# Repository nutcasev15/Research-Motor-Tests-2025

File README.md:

# Research Motor Tests 2025
FireSide PCB & Firmware and GroundSide Software

## Project Overview
This repository contains the support equipment and software developed for the 2025 research motor test campaign. The project includes both the **FireSide** embedded system with its PCB design (responsible for ignition, data sampling, and SD card logging) and the **GroundSide** software telemetry & command interface.

---

## Test Execution Hardware
The `pcb` directory contains the FireSide PCB schematics, design, and manufacturing Bill of Materials as a KiCAD 9.0 project. The FireSide system includes ignition control, data acquisition, and high speed logging built around a Nucleo32 STM32L412KB board. Key capabilities include:

- Upto 6 parallel >3 kHz channels logging using 12-bit ADC with a circular buffer
- Binary logging to SD card with onboard CSV conversion utility
- Reyax RYLR LoRa‑based command, debugging, and telemetry exchange
- MOSFET D4184 module‑based ignition control with safety interlocks
- Deterministic, debugger ready, and reliable state‑machine‑driven operation

This architecture aims to improve fault detection, reliability, and repeatability. The architecture is inspired by ECSS requirements on space operations software and commercial electronic components.

## Test Execution Software
The `src` directory contains the embedded & Python software developed for the test campaign.

### FireSide PCB Firmware (`src/FireSide/`)

| File | Description |
|------|-------------|
| **main.cpp** | Assembles the system state machine and runs the main execution loop. |
| **States.cpp** | Implements the BOOT, SAFE, ARM, LAUNCH, LOGGING, CONVERT & FAILURE states. Defines the state transition logic. |
| **DMADAQ.cpp** | Configures DMA‑based ADC sampling and SD card logging through the STM32 L4 HAL. |
| **Interfaces.hpp** | Defines shared HW interfaces for UART serials, IO pins and ADC hardware used across the FireSide firmware. Allows debugging through a USB Serial Monitor. |
| **ConvertLog.py** | Post‑processes FireSide binary log files into CSV format. Useful after testing to extract sensor data from large files if onboard conversion fails. |

### GroundSide (`src/GroundSide/`)

| File | Description |
|------|-------------|
| **GroundSide.py** | Sends commands and receives telemetry from the FireSide PCB via a Reyax RYLR LoRa chip through a USB-Serial module. Provides a traceable interface for executing a motor test. |

---

## References

1. [STM32 Nucleo‑32 Boards (MB1180) User Manual](
  https://www.st.com/resource/en/user_manual/um1956-stm32-nucleo32-boards-mb1180-stmicroelectronics.pdf
)
2. [STM32L4 HAL and Low‑Layer Drivers](
  https://www.st.com/resource/en/user_manual/um1884-description-of-stm32l4l4-hal-and-lowlayer-drivers-stmicroelectronics.pdf
)
3. [STM32L41x/42x/43x/44x/45x/46x Reference Manual](
  https://www.st.com/resource/en/reference_manual/rm0394-stm32l41xxx42xxx43xxx44xxx45xxx46xxx-advanced-armbased-32bit-mcus-stmicroelectronics.pdf
)
4. [Cortex‑M4 Programming Manual](
  https://www.st.com/resource/en/programming_manual/pm0214-stm32-cortexm4-mcus-and-mpus-programming-manual-stmicroelectronics.pdf
)
5. [STM32L412xx/422xB Device Errata](
  https://www.st.com/resource/en/errata_sheet/es0456-stm32l412xx422xb-device-errata-stmicroelectronics.pdf
)
6. [PlatformIO STM32 Platform Documentation](
  https://docs.platformio.org/en/latest/platforms/ststm32.html
)
7. [Reyax RYLR993 Transceiver Module](
  https://robu.in/product/reyax-rylr993_lite-868-915mhz-lorawan-transceiver-module-helium-compatible-lite-evaluation-boarddip-version/
)
8. [CP2102 USB to TTL Serial Converter Module](
  https://robu.in/product/cp-2102-6-pin/
)

---

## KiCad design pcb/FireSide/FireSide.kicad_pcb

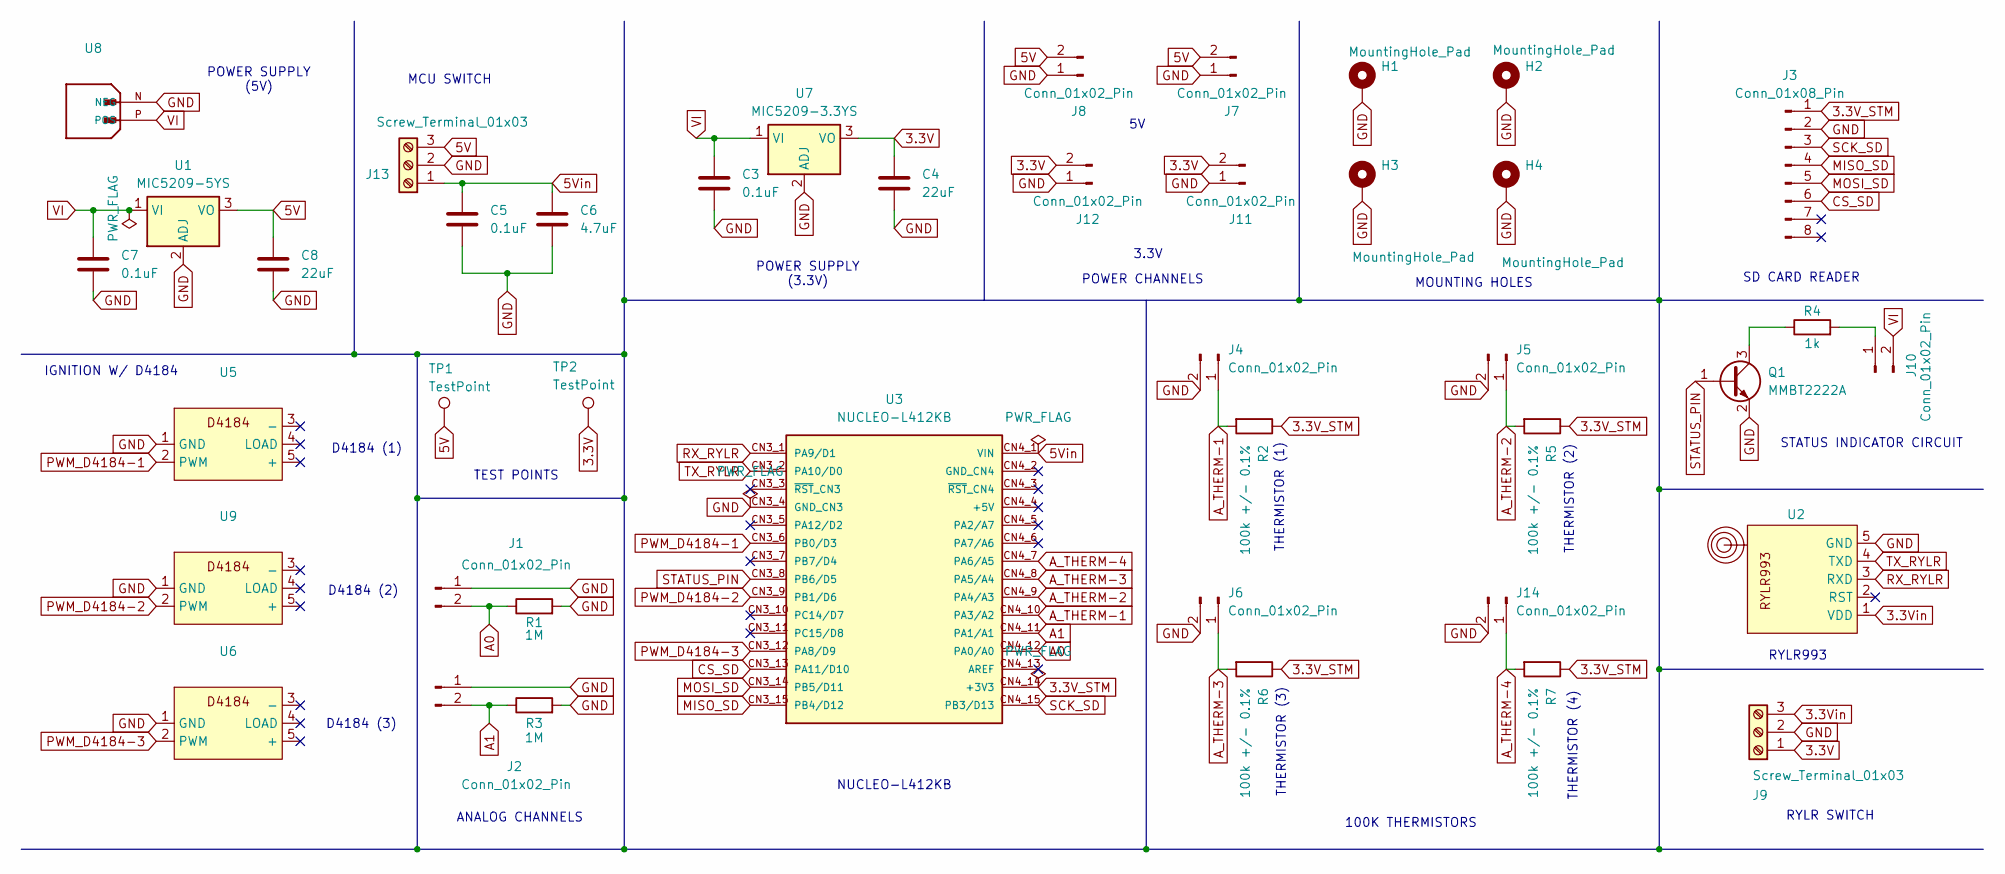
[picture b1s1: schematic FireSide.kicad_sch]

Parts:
C3, C5, C7: 0.1uF; C_0805_2012Metric
C4, C8: 22uF; C_0805_2012Metric
C6: 4.7uF; C_0805_2012Metric
H1, H2, H3, H4: MountingHole_Pad; MountingHole_4.3mm_M4_DIN965_Pad
J1, J2, J4, J5, J6, J7, J8, J10, J11, J12, J14: Conn_01x02_Pin; JST_XH_B2B-XH-A_1x02_P2.50mm_Vertical
J3: Conn_01x08_Pin; PinHeader_1x08_P2.54mm_Vertical
J9, J13: Screw_Terminal_01x03; TerminalBlock_MaiXu_MX126-5.0-03P_1x03_P5.00mm
Q1: MMBT2222A; SOT-23
R1, R3: 1M; R_Axial_DIN0204_L3.6mm_D1.6mm_P5.08mm_Horizontal
R2, R5, R6, R7: 100k +/- 0.1%; R_0805_2012Metric
R4: 1k; R_0805_2012Metric
TP1, TP2: TestPoint; TestPoint_Loop_D2.60mm_Drill1.6mm_Beaded
U1: MIC5209-5YS; SOT-223-3_TabPin2
U2: RYLR993
U3: NUCLEO-L412KB; PARTREV 8
U5, U6, U9: D4184
U7: MIC5209-3.3YS; SOT-223-3_TabPin2
U8: XT60-M

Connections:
3.3V: C4.1, J9.1, J11.2, J12.2, TP2.1, U7.3 (VO)
3.3V_STM: J3.1, R2.1, R5.1, R6.1, R7.1, U3.CN4_14 (+3V3)
3.3Vin: J9.3, U2.1 (VDD)
5V: C8.1, J7.2, J8.2, J13.3, TP1.1, U1.3 (VO)
5Vin: C5.1, C6.1, J13.1, U3.CN4_1 (VIN)
A0: J1.2, R1.1, U3.CN4_12 (PA0/A0)
A1: J2.2, R3.1, U3.CN4_11 (PA1/A1)
A_THERM-1: J4.1, R2.2, U3.CN4_10 (PA3/A2)
A_THERM-2: J5.1, R5.2, U3.CN4_9 (PA4/A3)
A_THERM-3: J6.1, R6.2, U3.CN4_8 (PA5/A4)
A_THERM-4: J14.1, R7.2, U3.CN4_7 (PA6/A5)
CS_SD: J3.6, U3.CN3_13 (PA11/D10)
GND: C3.2, C4.2, C5.2, C6.2, C7.2, C8.2, H1.1, H2.1, H3.1, H4.1, J1.1, J2.1, J3.2, J4.2, J5.2, J6.2, J7.1, J8.1, J9.2, J11.1, J12.1, J13.2, J14.2, Q1.2 (E), R1.2, R3.2, U1.2 (ADJ), U2.5 (GND), U3.CN3_4 (GND_CN3), U5.1 (GND), U6.1 (GND), U7.2 (ADJ), U8.N (NEG), U9.1 (GND)
MISO_SD: J3.4, U3.CN3_15 (PB4/D12)
MOSI_SD: J3.5, U3.CN3_14 (PB5/D11)
unnamed: J10.1, R4.2
unnamed: Q1.3 (C), R4.1
PWM_D4184-1: U3.CN3_6 (PB0/D3), U5.2 (PWM)
PWM_D4184-2: U3.CN3_9 (PB1/D6), U9.2 (PWM)
PWM_D4184-3: U3.CN3_12 (PA8/D9), U6.2 (PWM)
RX_RYLR: U2.3 (RXD), U3.CN3_1 (PA9/D1)
SCK_SD: J3.3, U3.CN4_15 (PB3/D13)
STATUS_PIN: Q1.1 (B), U3.CN3_8 (PB6/D5)
TX_RYLR: U2.4 (TXD), U3.CN3_2 (PA10/D0)
VI: C3.1, C7.1, J10.2, U1.1 (VI), U7.1 (VI), U8.P (POS)

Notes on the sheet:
D4184 (3)
RYLR993
THERMISTOR (4)
THERMISTOR (1)
IGNITION W/ D4184
SD CARD READER
STATUS INDICATOR CIRCUIT
THERMISTOR (3)
3.3V
THERMISTOR (2)
POWER SUPPLY (5V)
NUCLEO-L412KB
ANALOG CHANNELS
POWER SUPPLY (3.3V)
POWER CHANNELS
RYLR SWITCH
100K THERMISTORS
TEST POINTS
MOUNTING HOLES
D4184 (1)
D4184 (2)
MCU SWITCH

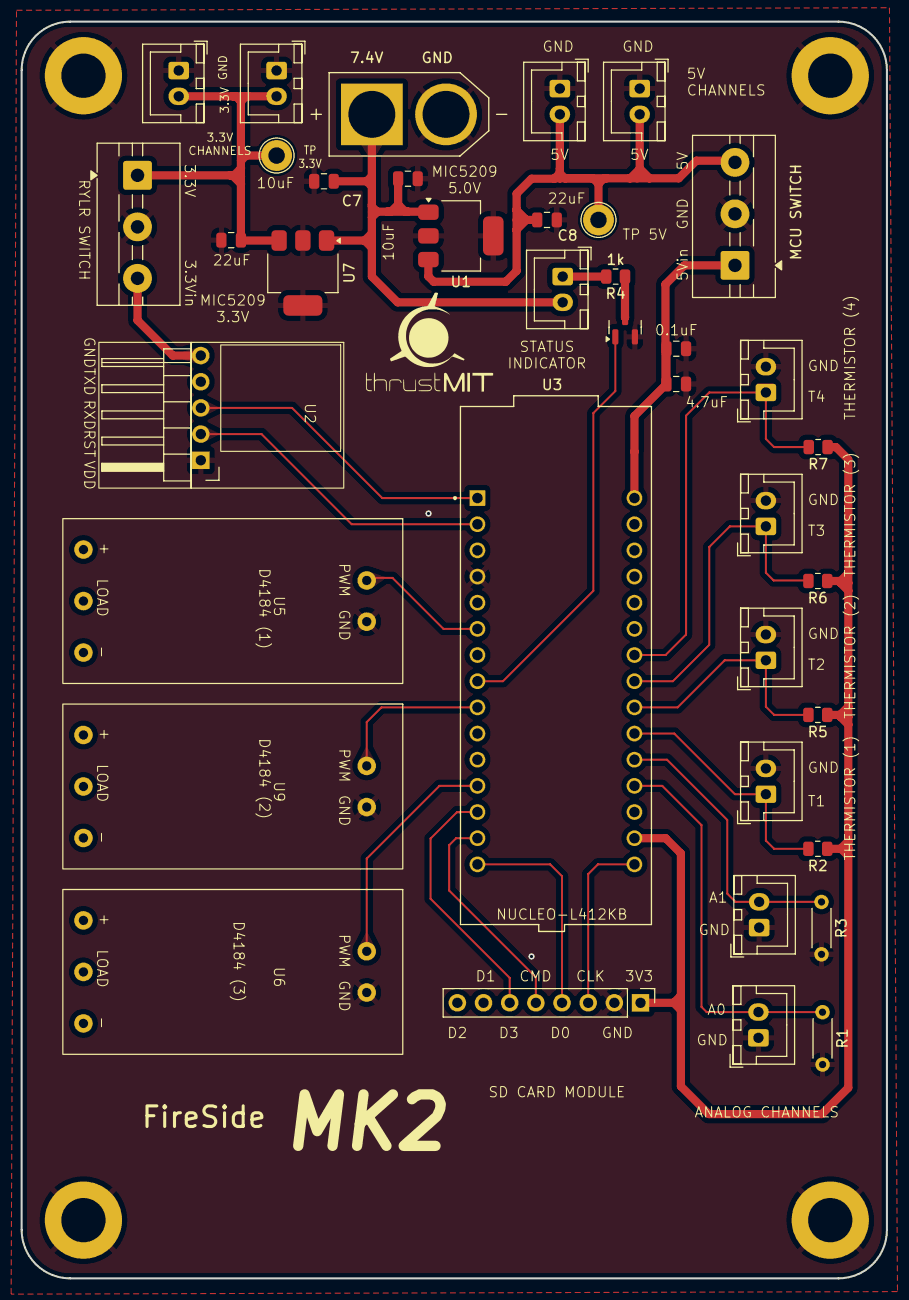
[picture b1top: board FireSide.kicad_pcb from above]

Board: 2 copper layers, 84.0 x 122.0 mm, 43 parts (0 on the bottom side), 25 nets.

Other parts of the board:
L0: TMIT; TMIT-Logo

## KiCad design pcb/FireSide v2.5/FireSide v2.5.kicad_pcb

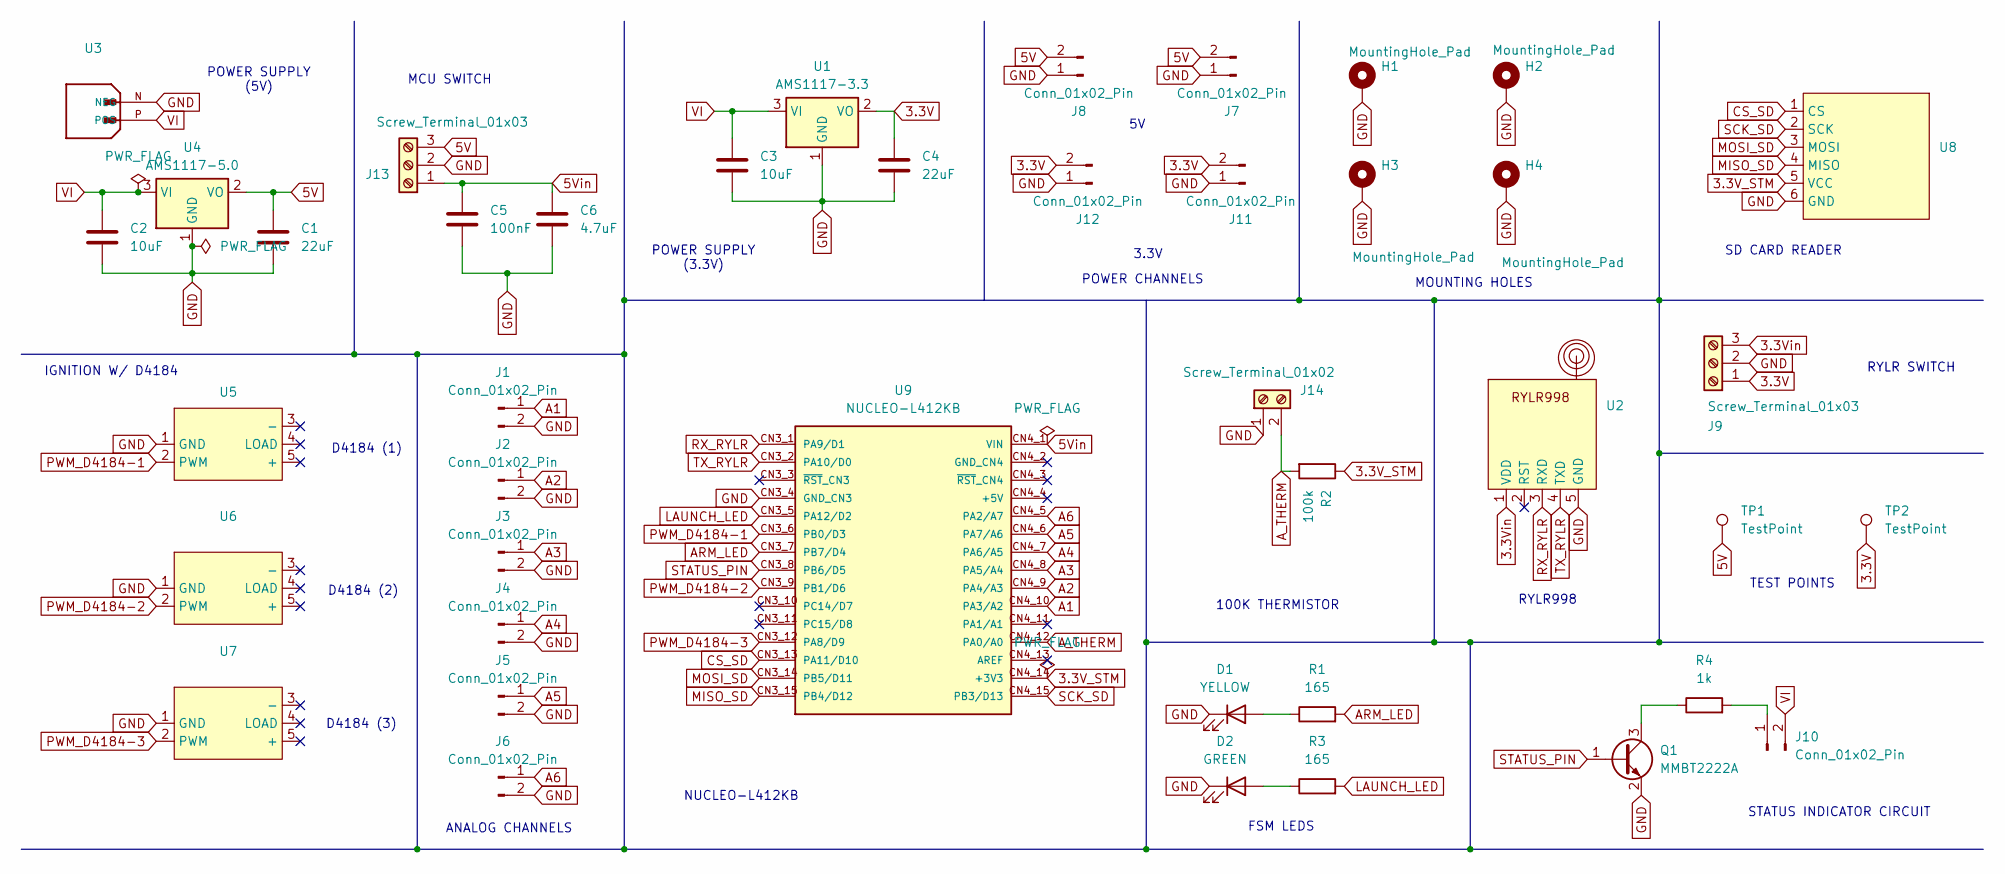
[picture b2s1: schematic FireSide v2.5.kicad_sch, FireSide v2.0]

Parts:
C1, C4: 22uF; C_0805_2012Metric
C2, C3: 10uF; C_0805_2012Metric
C5: 100nF; C_0805_2012Metric
C6: 4.7uF; C_0805_2012Metric
D1: YELLOW; LED_0805_2012Metric
D2: GREEN; LED_0805_2012Metric
H1, H2, H3, H4: MountingHole_Pad; MountingHole_4.3mm_M4_DIN965_Pad
J1, J2, J3, J4, J5, J6, J10: Conn_01x02_Pin; JST_EH_B2B-EH-A_1x02_P2.50mm_Vertical
J7, J8, J11, J12: Conn_01x02_Pin; PinHeader_1x02_P2.54mm_Vertical
J9, J13: Screw_Terminal_01x03; TerminalBlock_bornier-3_P5.08mm
J14: Screw_Terminal_01x02; TerminalBlock_bornier-2_P5.08mm
Q1: MMBT2222A; SOT-23
R1, R3: 165; R_0805_2012Metric
R2: 100k; R_Axial_DIN0204_L3.6mm_D1.6mm_P5.08mm_Horizontal
R4: 1k; R_0805_2012Metric
TP1, TP2: TestPoint; TestPoint_Loop_D2.60mm_Drill1.6mm_Beaded
U1: AMS1117-3.3; SOT-223-3_TabPin2
U2: RYLR998
U3: XT60-M
U4: AMS1117-5.0; SOT-223-3_TabPin2
U5, U6, U7: D4184
U8: SD Card Reader
U9: NUCLEO-L412KB; NUCLEO L412KB; PARTREV 8

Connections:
3.3V: C4.1, J9.1, J11.2, J12.2, TP2.1, U1.2 (VO)
3.3V_STM: R2.1, U8.5 (VCC), U9.CN4_14 (+3V3)
3.3Vin: J9.3, U2.1 (VDD)
5V: C1.1, J7.2, J8.2, J13.3, TP1.1, U4.2 (VO)
5Vin: C5.1, C6.1, J13.1, U9.CN4_1 (VIN)
A1: J1.1, U9.CN4_10 (PA3/A2)
A2: J2.1, U9.CN4_9 (PA4/A3)
A3: J3.1, U9.CN4_8 (PA5/A4)
A4: J4.1, U9.CN4_7 (PA6/A5)
A5: J5.1, U9.CN4_6 (PA7/A6)
A6: J6.1, U9.CN4_5 (PA2/A7)
ARM_LED: R1.2, U9.CN3_7 (PB7/D4)
A_THERM: J14.2, R2.2, U9.CN4_12 (PA0/A0)
CS_SD: U8.1 (CS), U9.CN3_13 (PA11/D10)
GND: C1.2, C2.2, C3.2, C4.2, C5.2, C6.2, D1.1 (K), D2.1 (K), H1.1, H2.1, H3.1, H4.1, J1.2, J2.2, J3.2, J4.2, J5.2, J6.2, J7.1, J8.1, J9.2, J11.1, J12.1, J13.2, J14.1, Q1.2 (E), U1.1 (GND), U2.5 (GND), U3.N (NEG), U4.1 (GND), U5.1 (GND), U6.1 (GND), U7.1 (GND), U8.6 (GND), U9.CN3_4 (GND_CN3)
LAUNCH_LED: R3.2, U9.CN3_5 (PA12/D2)
MISO_SD: U8.4 (MISO), U9.CN3_15 (PB4/D12)
MOSI_SD: U8.3 (MOSI), U9.CN3_14 (PB5/D11)
unnamed: D1.2 (A), R1.1
unnamed: D2.2 (A), R3.1
unnamed: J10.1, R4.2
unnamed: Q1.3 (C), R4.1
PWM_D4184-1: U5.2 (PWM), U9.CN3_6 (PB0/D3)
PWM_D4184-2: U6.2 (PWM), U9.CN3_9 (PB1/D6)
PWM_D4184-3: U7.2 (PWM), U9.CN3_12 (PA8/D9)
RX_RYLR: U2.3 (RXD), U9.CN3_1 (PA9/D1)
SCK_SD: U8.2 (SCK), U9.CN4_15 (PB3/D13)
STATUS_PIN: Q1.1 (B), U9.CN3_8 (PB6/D5)
TX_RYLR: U2.4 (TXD), U9.CN3_2 (PA10/D0)
VI: C2.1, C3.1, J10.2, U1.3 (VI), U3.P (POS), U4.3 (VI)

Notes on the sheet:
D4184 (3)
FSM LEDS
RYLR998
IGNITION W/ D4184
SD CARD READER
STATUS INDICATOR CIRCUIT
3.3V
POWER SUPPLY (5V)
NUCLEO-L412KB
ANALOG CHANNELS
POWER SUPPLY (3.3V)
POWER CHANNELS
RYLR SWITCH
100K THERMISTOR
TEST POINTS
MOUNTING HOLES
D4184 (1)
D4184 (2)
MCU SWITCH

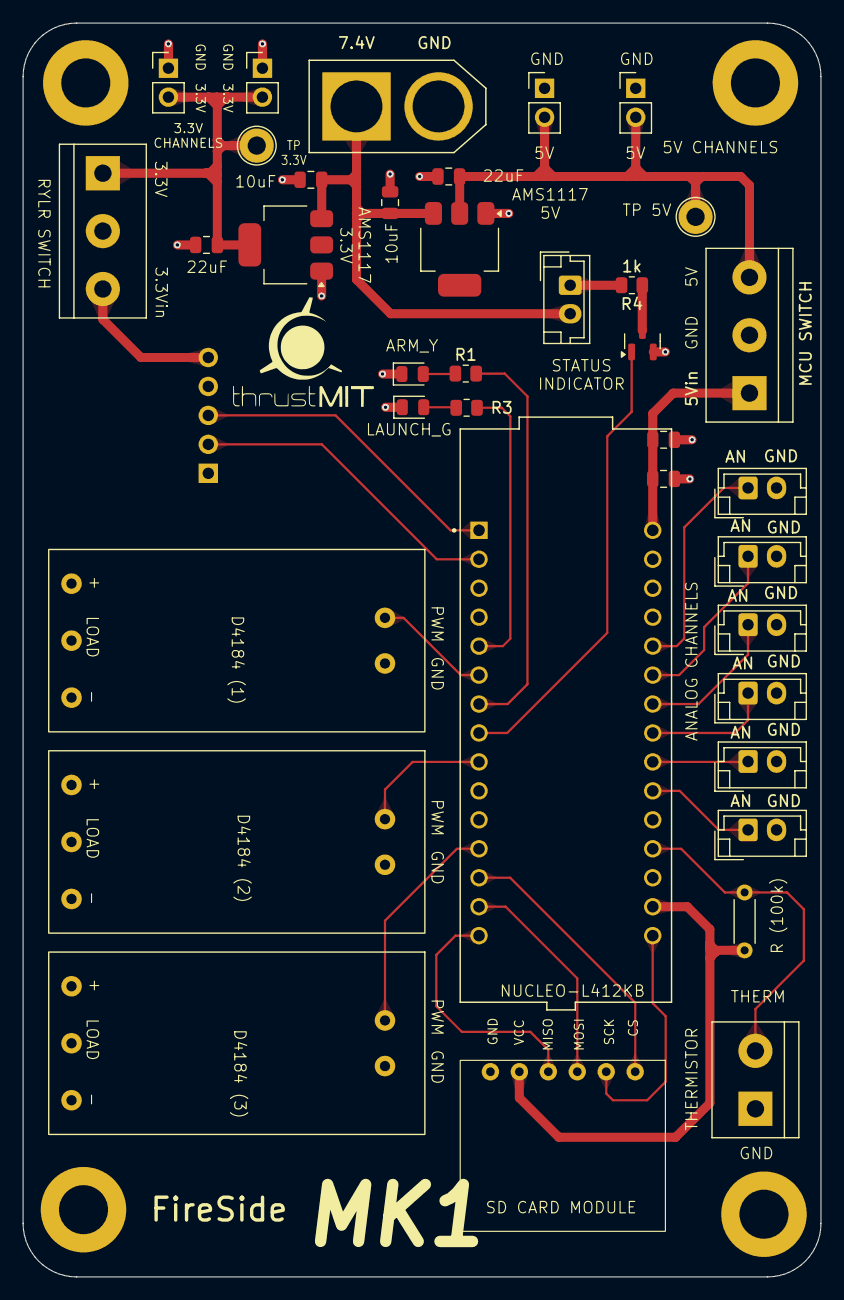
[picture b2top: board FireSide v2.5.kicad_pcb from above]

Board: 2 copper layers, 70.0 x 110.0 mm, 42 parts (1 on the bottom side), 30 nets.

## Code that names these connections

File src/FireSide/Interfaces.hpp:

#ifndef _INTERFACES_H_
#define _INTERFACES_H_
// #### Library Headers
// Arduino Framework and Data Types
#include <Arduino.h>

// STM32 L4 Board HAL Include
#include <stm32l4xx_hal.h>
// Disable Arduino Framework Access to ADC
#define HAL_ADC_MODULE_ONLY

// SPI Hardware Driver for SD Card IO
#include <SPI.h>

// File Class for Binary Data Container
#include <SD.h>


// #### STM32 L412KB Pin Configuration
// Status Pin for Visual Output
#define STATUS_PIN 2

// MOSFET Latch Pins for Firing Igniters
#define FIRE_PIN_A 3
#define FIRE_PIN_B 6
#define FIRE_PIN_C 9
// D4184 Input Firing Logic
#define STATUS_FIRE HIGH
#define STATUS_SAFE LOW


// #### Serial Communication Interface Configuration
// RYLR993 Hardware Interface
// See REYAX RYLR993 Datasheet for UART Configuration
#define RYLR_UART_BAUD 9600UL

// #define USE_USB_SERIAL
#ifdef USE_USB_SERIAL
// Redirect RYLR to USB Communications and STLink Serial
#define RYLR Serial
#else
// Link Hardware Serial (Pins D0 & D1) to RYLR
// See CN4 on Page 29 of MB1180 Nucleo L412KB Board User Manual
#define RYLR_UART_TX PA9
#define RYLR_UART_RX PA10
inline HardwareSerial RYLR(RYLR_UART_RX, RYLR_UART_TX);
#endif

// Poll RYLR Module & Parse Incoming GroundSide Commands
inline void ParseRYLR(String &Buffer)
{
  // Setup Persistent Receive Buffer
  static String parsed;
  parsed.reserve(64UL);

#ifndef USE_USB_SERIAL
  // Clear Receive Buffer
  parsed = "";

  // Check if Data is from GroundSide
  // See +RCV in REYAX AT RYLRX93 Commanding Datasheet
  // https://reyax.com//products/RYLR993
  while (parsed.indexOf("+RCV") == -1)
  {
    // Delay to Allow GroundSide Personnel to Respond
    delay(250UL);
    parsed = RYLR.readStringUntil('\n');
  }
#else
  // Wait Until USB Serial Sends Data
  while (!RYLR.available())
  {
    delay(500UL);
  }

  // Load Data from USB Serial Monitor
  parsed = RYLR.readStringUntil('\n');
#endif

  // Extract Data from Parsed String
  // See +RCV in REYAX AT RYLRX93 Commanding Datasheet
  // https://reyax.com//products/RYLR993
  // Remove Data from Last 2 Fields
  parsed.remove(parsed.lastIndexOf(','));
  parsed.remove(parsed.lastIndexOf(','));

  // Extract Data in 3rd Comma Separated Field
  Buffer = parsed.substring(parsed.lastIndexOf(',') + 1);

  // Strip Carriage Return
  Buffer.trim();

  return;
}

// Send Data to GroundSide via RYLR Module
inline void SendRYLR(const String &Data)
{
  // Setup Persistent Response Buffer
  static String response;
  response.reserve(64UL);

  // Clear Past RYLR Responses to SEND Commands
  response = "";

  // Issue Send AT Command
  // See +SEND in REYAX AT RYLRX93 Commanding Datasheet
  // https://reyax.com//products/RYLR993
  RYLR.print("AT+SEND=0,");

  // Issue Payload Length Including Header
  RYLR.print(Data.length() + 4);

  // Issue FireSide PCB Header
  RYLR.print(",FS> ");

  // Issue Data and Complete Command with Line End
  // CRLF Line End is Mandatory
  RYLR.print(Data);
  RYLR.print("\r\n");

#ifndef USE_USB_SERIAL
  // Wait for RYLR Response to SEND Command
  while (response.length() == 0)
  {
    // Delay to Allow RYLR to Respond
    delay(250UL);
    response = RYLR.readStringUntil('\n');

    // Remove Newline & Whitespace Characters
    response.trim();
  }

  // Send Debug Data if Transmission Fails
  // See +SEND in REYAX AT RYLRX93 Commanding Datasheet
  // https://reyax.com//products/RYLR993
  if (response.indexOf("OK") == -1)
  {
    // Try to Communicate Error to GroundSide
    // Often GroundSide Receives Data Despite FireSide Errors
    SendRYLR(response);
  }
#endif

  return;
}


// #### STM32 L412KB ADC-DMA Configuration
// Number of Concurrently Logged ADC Channels
// 2 Channels Correspond to A0 & A1 on Pinout
// 4 Channels Correspond to A0 to A3 on Pinout
// 6 Channels Correspond to A0 to A5 on Pinout
#define ADC_PARALLEL_CHANNELS 6

// See CN4 on Page 29 of MB1180 Nucleo L412KB Board User Manual
#define MAX_PARALLEL_CHANNELS 6
#if ADC_PARALLEL_CHANNELS < 1 || ADC_PARALLEL_CHANNELS > MAX_PARALLEL_CHANNELS
#error "Too Few or Too Many ADC Channels Configured for Logging"
#error "Minimum Configured Channels = 1"
#error "Maximum Configured Channels = 6"
#endif

// ADC Pins, Channel and Rank Configuration Structure
// Wrap HAL Defines into Arrays for Pin and Channel Configuration
// See CN4 on Page 29 of MB1180 Nucleo L412KB Board User Manual
struct ADCHardwareConfig {
  uint8_t pin;
  uint32_t pad;
  uint32_t channel;
  uint32_t rank;
};

const ADCHardwareConfig ADCHardwareSetup[] = {
  {PIN_A0, PA0, ADC_CHANNEL_5, ADC_REGULAR_RANK_1},
  {PIN_A1, PA1, ADC_CHANNEL_6, ADC_REGULAR_RANK_2},
  {PIN_A2, PA3, ADC_CHANNEL_8, ADC_REGULAR_RANK_3},
  {PIN_A3, PA4, ADC_CHANNEL_9, ADC_REGULAR_RANK_4},
  {PIN_A4, PA5, ADC_CHANNEL_10, ADC_REGULAR_RANK_5},
  {PIN_A5, PA6, ADC_CHANNEL_11, ADC_REGULAR_RANK_6}
};


// #### Error Definitions
// Throw this if ADC HAL Initialisation Fails
#define ERR_HAL_ADC 1
// Throw this if DMA HAL Initialisation Fails
#define ERR_HAL_DMA 2
// Throw this if SD Card Initialisation Fails
#define ERR_SD_INIT 3
// Throw this if File is not Available
#define ERR_SD_FILE 4
// Throw this if SD Data Buffer is not Free
#define ERR_SD_BUFF 5

// Indicate Error on Status Pin
inline void ErrorBlink(uint8_t CODE)
{
  // Set Blink Repeating Interval (ms)
  const uint16_t period = 5000;

  // Assemble and Transmit Status over RYLR
  String status = "Error Code: ";
  status += CODE;
  SendRYLR(status);

  // Turn Indicator LED Off
  digitalWrite(STATUS_PIN, LOW);
  // Blink CODE Number of Times, Then Wait and Repeat
  while (1)
  {
    for (short i = 0; i < CODE; i++)
    {
      digitalWrite(STATUS_PIN, HIGH);
      delay(period / (2 * CODE));
      digitalWrite(STATUS_PIN, LOW);
      delay(period / (2 * CODE));
    }
    delay(period / 2);
  }
}

#endif

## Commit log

2025-03-22 Added current files
2025-03-23 Update groundside.ino
    at line 62, the currentState was still LAUNCH and not DONE, so the switch was never going in DONE case at testbed uno
2025-03-24 Testbed MKR code
    PlatformIO Project
2025-03-24 Renamed folder DAQ to testbed_MKR
2025-05-02 [GIT] Create Top Level Ignore File
2025-05-02 [PIO] Move Project Configuration to Top Level
2025-05-02 [PIO] Restructure Project with Two Environments
2025-05-04 [PIO] Update Library Includes for all Environments
2025-05-04 [GS] Remove State Machine Implementation in GroundSide UNO Code
2025-05-04 [FS] Refactor and Unify DAQ Code with Finite State Machine
2025-05-04 [FS] Refactor Python Binary Log File Convertor
2025-05-05 [GS] Remove Prefix in Serial Outputs to Avoid Confusion
2025-05-05 [FS] Optimise C/C++ Binary Log Conversion Routine
2025-05-05 [FS] Shorten Comments in C/C++
2025-05-05 [FS] Cosmetic Changes to Comments and Serial Outputs
2025-05-05 [FS] Fix SD Not Initialised Bug After Conversion
2025-05-05 [FS] Improve Scope of Failure State Diagnostics
2025-05-05 Optimise String Library Usage for FireSide and GroundSide
2025-05-06 [FS] Create FireSide Board Schematics
2025-05-06 [FS] Correct Igniter Firing Logic to Inverted Logic
2025-05-06 [FS] Create PCB Board Design
2025-05-06 [FS] Fix Unintended Igniter Firing Bug at Startup
2025-05-11 [GS] Fix Malformed AT Send Command Bug
2025-05-11 [FS] Cosmetic Changes to Logging Outputs
2025-05-11 [FS] Cosmetic Corrections to Python Script Comments
2025-05-11 [FS] Call Return After Call to ErrorBlink Function
2025-05-25 [GIT] Ignore KiCAD Editing Lock File
2025-05-25 [FS] Update PCB to 120x80 mm and Use JST Connectors
2025-07-19 [GS] Transition to Python USB Serial Implementation for GroundSide
2025-07-28 [FS] Adapt Code to Nucleo L412KB using STM L4 HAL
2025-07-29 [FS] Correct State Transition and Predicate Implementation
2025-07-29 Utilise Line Endings for Delimiting RYLR Transmissions
2025-07-29 [FS] Fix OSC-32K and D8 Pin Conflict
2025-08-03 [FS] Strip White Space and Line Endings in RYLR Commands
2025-08-03 [FS] Debug Single Shot Analog Pin Readouts and Extend to 7 Pin Logging
2025-08-03 [FS] Debug Static Variable Definitions and Reduce Global Variable Usage
2025-08-09 [FS] Optimise Binary Log File Buffer Format for SD Write
2025-08-09 [FS] Correct STM32 HAL Interrupt Callbacks and Peripheral Configuration
2025-08-09 [FS] Increase SD Card SPI Clock Rates to 20 MHz
2025-08-09 [FS] Fix Incorrect File Name Check
2025-08-09 [FS] Clean Up Arduino String Manipulation Code for File IO
2025-08-09 [FS] Decrease File System IO to Reduce Stress on SD Card
2025-08-24 [FS] Fix CRLF AT Command Bug in RYLR Interface
2025-08-24 [FS] Check SD Card State Before ARM Procedure Completion
2025-08-24 [FS] Reduce High Speed Bus Bandwidth and Avoid Resource Conflicts
2025-08-24 [FS] Fix DMA Buffer Overrun and Bus Fault
2025-08-24 [FS] Cosmetic Changes to Code Comments
2025-08-24 [FS] Only Terminate Logging on Receipt of Newline
2025-08-24 [FS] Fix Binary Data Readout Misalignment and Timestamp Calculation
2025-08-26 [FS] Transition PCB to Nucleo L412KB and SMD Components
2025-09-23 [FS] Updated PCB files to v2.5
2025-10-05 [FS] PCB Updated to v1.1.6
2026-01-18 [FS] Disable AT Command Checks on USB Serial
2026-01-18 Shift to RYLR993 Default on GroundSide and FireSide
2026-01-18 [FS] Report Debug Data on RYLR Error Instead
2026-01-18 [FS] Change Polling from STM32 Serial to RYLR Responses
2026-01-18 [FS] Skip RYLR Boot & Response Checks on USB Serial Link
2026-01-18 [FS] Improve USB Serial Debugging UX
2026-01-18 [GS] Correct AT Commanding Sequence & Checks
2026-01-18 [GS] Fix Command Request Bug from RSSI Reporting
2026-01-18 [FS] Readout Raw Analog Channel Data
2026-01-19 [GS] Add Local Logging Support
2026-01-19 Reduce Latency in RYLR Interfaces to 100ms
2026-01-20 Revert "Reduce Latency in RYLR Interfaces to 100ms"
    This reverts commit 39dadd360af1746bcde35fad65637af7eb3f1ce5.
2026-01-21 Reduce RYLR Latency to 250ms
2026-01-21 [GS] Logging Label and Cosmetic Changes
2026-01-21 Ensure RYLR Response Buffers Clear on Read
2026-01-21 Update README and LICENSE for Release
2026-01-21 [GS] Improve UX and FireSide Telemetry Formatting
2026-01-21 [README] Happy New Year: 2026
2026-01-21 [GS] Align Formatting & More Cosmetic Changes
2026-01-21 [GS] Handle Type Mismatch in RYLR Parsing
2026-01-21 [FS] Revert trim in relayer parsing
2026-01-21 [GS] Compatibility for Python<=3.13
2026-02-07 [FS] Updated FireSide PCB with RYLR993
2026-02-22 [FS] Updated PCB (v1.2.0)
2026-03-28 [FS] Remove AMS1117 Regulators & Apply ECSS-E-ST-20-21C Standard
